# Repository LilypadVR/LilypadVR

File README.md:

# LilypadVR
 Full Body Tracking for VR, based on SlimeVR

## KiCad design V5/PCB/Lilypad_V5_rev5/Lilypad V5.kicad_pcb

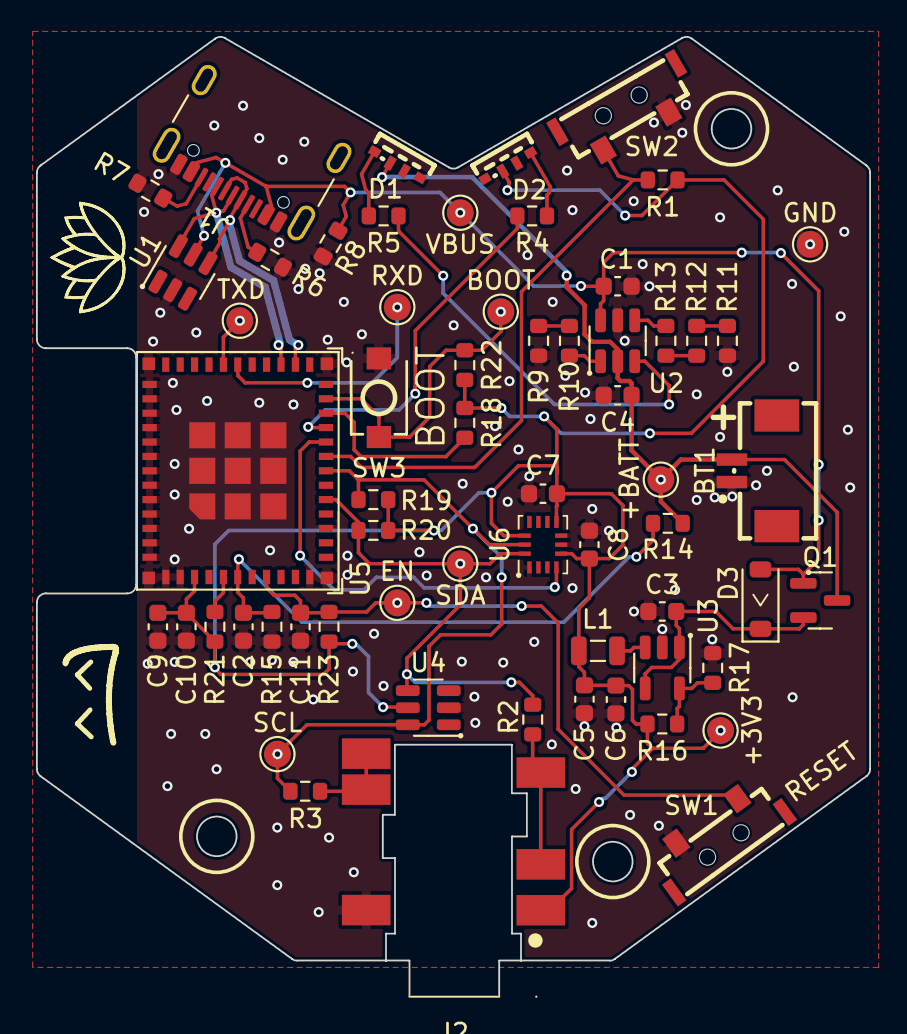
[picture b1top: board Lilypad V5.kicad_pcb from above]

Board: 2 copper layers, 46.3 x 53.3 mm, 61 parts (0 on the bottom side), 33 nets.

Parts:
BT1: Micro-JST; CONN-SMD_2P-P1.25_XUNPU_WAFER-MX1.25-2PWB
C1, C3, C4, C5, C6, C10: 4.7uF; C_0603_1608Metric
C2, C7, C8, C9, C11: 100nF; C_0603_1608Metric
D1: CHARGING_LED; LED-SMD_FM-3510RGBA-SG
D2: STATUS_LED; LED-SMD_FM-3510RGBA-SG
D3: 1N5817W; D_SOD-123
J1: USB-C; USB_C_Receptacle_GCT_USB4105-xx-A_16P_TopMnt_Horizontal
J2: TRRS; AUDIO-SMD_PJ-342C-1
L1: 4.7uH; L_0806_2012Metric
Q1: AO3401A; SOT-23
R1, R6, R7, R9, R10, R18, R19, R20, R21, R22, R23: 5k1; R_0603_1608Metric
R2, R3, R11, R12, R13: 220R; R_0603_1608Metric
R4, R5: 3k; R_0603_1608Metric
R8, R14, R15, R17: 150k; R_0603_1608Metric
R16: 680k; R_0603_1608Metric
SW1: BTN_RESET; SW-SMD_TS-KG012EV
SW2: BTN_USER; SW-SMD_TS-KG012EV
SW3: BTN_BOOT; SW-SMD_L3.9-W3.0-P4.45
TP1: VBUS; TestPoint_Pad_D1.5mm
TP2: +BATT; TestPoint_Pad_D1.5mm
TP3: +3V3; TestPoint_Pad_D1.5mm
TP4: SCL; TestPoint_Pad_D1.5mm
TP5: SDA; TestPoint_Pad_D1.5mm
TP6: TXD; TestPoint_Pad_D1.5mm
TP7: RXD; TestPoint_Pad_D1.5mm
TP8: EN; TestPoint_Pad_D1.5mm
TP9: BOOT; TestPoint_Pad_D1.5mm
TP10: GND; TestPoint_Pad_D1.5mm
U1, U4: SRV05-4; SOT-23-6
U2: BQ21040; SOT-23-6
U3: M3406; SOT-23-5
U5: ESP32-C3-MINI-1-N4; ESP32-C3-MINI-1
U6: BMI270; Bosch_LGA-14_3x2.5mm_P0.5mm

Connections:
+3V3: C5.1, C6.1, C7.2, C8.1, C9.1, C10.1, D2.2 (A), J2.1, L1.2, R1.2, R16.1, R18.2, R19.2, R20.2, R21.2, R22.2, R23.1, TP3.1, U4.5, U5.3 (3V3), U6.5 (VDDIO), U6.8 (VDD), U6.12 (CSB)
+BATT: BT1.1 (+), C4.1, D1.2 (A), Q1.3 (D), R14.1, TP2.1, U2.2 (OUT)
ADC: C2.2, R14.2, R15.1, U5.6 (IO3)
BOOT: R22.1, SW3.1, TP9.1, U5.23 (IO9)
CHRG_LED: R5.2, U2.3 (~CHG)
D+: J1.A6 (D+), J1.B6 (D+), U1.6, U5.27 (IO19)
D-: J1.A7 (D-), J1.B7 (D-), U1.4, U5.26 (IO18)
EN: C11.1, R23.2, SW1.1, TP8.1, U5.8 (EN)
GND: BT1.2 (-), C1.2, C2.1, C3.2, C4.2, C5.2, C6.2, C7.1, C8.2, C9.2, C10.2, C11.2, J1.A1 (GND), J2.2, R6.1, R7.2, R8.2, R9.1, R11.2, R15.2, R17.2, SW1.2, SW2.2, SW3.2, TP10.1, U1.2, U2.5 (GND), U3.2 (GND), U4.2, U5.1 (GND), U5.2 (GND), U5.11 (GND), U5.14 (GND), U5.36 (GND), U5.37 (GND), U5.38 (GND), U5.39 (GND), U5.40 (GND), U5.41 (GND), U5.42 (GND), U5.43 (GND), U5.44 (GND), U5.45 (GND), U5.46 (GND), U5.47 (GND), U5.48 (GND), U5.49 (GND), U5.50 (GND), U5.51 (GND), U5.52 (GND), U5.53 (GND), U6.1 (SDO), U6.6 (GNDIO), U6.7 (GND)
INT_MAIN: U5.20 (IO6), U6.4 (INT1)
IO2: R21.1, U5.5 (IO2)
IO8: R18.1, U5.22 (IO8)
unnamed: D1.1 (RK), R5.1
unnamed: D2.4 (BK), R4.1
unnamed: J1.A5 (CC1), R6.2
unnamed: J1.B5 (CC2), R7.1
unnamed: J2.3, R2.1
unnamed: J2.4, R3.1
unnamed: R9.2, R10.1
unnamed: R11.1, R12.2
unnamed: R12.1, R13.2
unnamed: R13.1, U2.4 (ISET)
unnamed: R10.2, U2.1 (TS)
unnamed: R16.2, R17.1, U3.5 (FB)
unnamed: L1.1, U3.3 (SW)
RXD: TP7.1, U5.30 (RXD0)
SCL: R3.2, R19.1, TP4.1, U4.6, U5.18 (IO4), U6.13 (SCx)
SDA: R2.2, R20.1, TP5.1, U4.4, U5.16 (IO10), U6.14 (SDx)
STATUS_LED: R4.2, U5.21 (IO7)
TXD: TP6.1, U5.31 (TXD0)
USER_IO: R1.1, SW2.1, U5.19 (IO5)
VBUS: C1.1, D3.2 (A), J1.A4 (VBUS), Q1.1 (G), R8.1, TP1.1, U1.5, U2.6 (VIN)
VCC: C3.1, D3.1 (K), Q1.2 (S), U3.1 (RUN), U3.4 (VIN)

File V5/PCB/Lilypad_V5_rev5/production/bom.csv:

Designator,Footprint,Quantity,Value,LCSC Part #
BT1,CONN-SMD_2P-P1.25_XUNPU_WAFER-MX1.25-2PWB,1,Micro-JST,C3029359
"C1, C10, C3, C4, C5, C6",0603,6,4.7uF,C19666
"C11, C2, C7, C8, C9",0603,5,100nF,C14663
D1,LED-SMD_FM-3510RGBA-SG,1,CHARGING_LED,C727903
D2,LED-SMD_FM-3510RGBA-SG,1,STATUS_LED,C727903
D3,D_SOD-123,1,1N5817W,C2828419
J1,USB_C_Receptacle_GCT_USB4105-xx-A_16P_TopMnt_Horizontal,1,USB-C,C2765186
J2,AUDIO-SMD_PJ-342C,1,TRRS,C2837091
L1,0806,1,4.7uH,C98335
Q1,SOT-23,1,AO3401A,C6575062
"R1, R10, R18, R19, R20, R21, R22, R23, R6, R7, R9",0603,11,5k1,C23186
"R11, R12, R13, R2, R3",0603,5,220R,C22962
"R14, R15, R17, R8",0603,4,150k,C22807
R16,0603,1,680k,C25822
"R4, R5",0603,2,3k,C4211
SW1,SW-SMD_TS-KG012EV,1,BTN_RESET,C410363
SW2,SW-SMD_TS-KG012EV,1,BTN_USER,C410363
SW3,SW-SMD_L3.9-W3.0-P4.45,1,BTN_BOOT,C720477
TP1,TestPoint_Pad_D1.5mm,1,VBUS,N/A
TP10,TestPoint_Pad_D1.5mm,1,GND,N/A
TP2,TestPoint_Pad_D1.5mm,1,+BATT,N/A
TP3,TestPoint_Pad_D1.5mm,1,+3V3,N/A
TP4,TestPoint_Pad_D1.5mm,1,SCL,N/A
TP5,TestPoint_Pad_D1.5mm,1,SDA,N/A
TP6,TestPoint_Pad_D1.5mm,1,TXD,N/A
TP7,TestPoint_Pad_D1.5mm,1,RXD,N/A
TP8,TestPoint_Pad_D1.5mm,1,EN,N/A
TP9,TestPoint_Pad_D1.5mm,1,BOOT,N/A
"U1, U4",SOT-23-6,2,SRV05-4,C7420376
U2,SOT-23-6,1,BQ21040,C202311
U3,SOT-23-5,1,M3406,C83224
U5,ESP32-C3-MINI-1,1,ESP32-C3-MINI-1-N4,C2838502
U6,Bosch_LGA-14_3x2.5mm_P0.5mm,1,BMI270,C2836813

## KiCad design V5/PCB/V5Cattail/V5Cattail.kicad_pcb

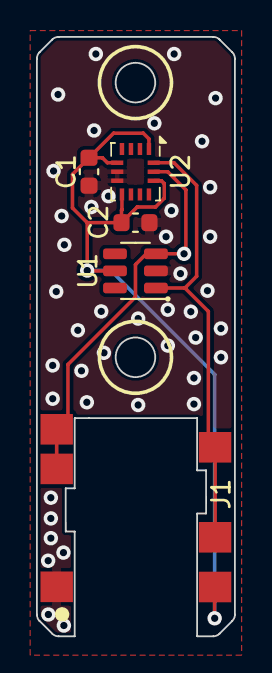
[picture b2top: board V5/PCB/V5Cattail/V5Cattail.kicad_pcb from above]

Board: 2 copper layers, 11.0 x 33.3 mm, 5 parts (0 on the bottom side), 4 nets.

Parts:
C1, C2: 100nF; C_0603_1608Metric
J1: TRRS; AUDIO-SMD_PJ-342C
U1: SRV05-4_C558418; SOT-23-6
U2: BMI270; Bosch_LGA-14_3x2.5mm_P0.5mm

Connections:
+3V3: C1.2, C2.1, J1.1, U1.5, U2.1 (SDO), U2.5 (VDDIO), U2.8 (VDD), U2.12 (CSB)
GND: C1.1, C2.2, J1.2, U1.2, U2.6 (GNDIO), U2.7 (GND)
SCL: J1.4, U1.3, U2.13 (SCx)
SDA: J1.3, U1.1, U2.14 (SDx)

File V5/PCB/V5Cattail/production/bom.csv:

Designator,Footprint,Quantity,Value,LCSC Part #
"C1, C2",0603,2,100nF,C14663
J1,AUDIO-SMD_PJ-342C,1,TRRS,C2837091
U1,SOT-23-6,1,SRV05-4_C558418,C558418
U2,Bosch_LGA-14_3x2.5mm_P0.5mm,1,BMI270,C2836813

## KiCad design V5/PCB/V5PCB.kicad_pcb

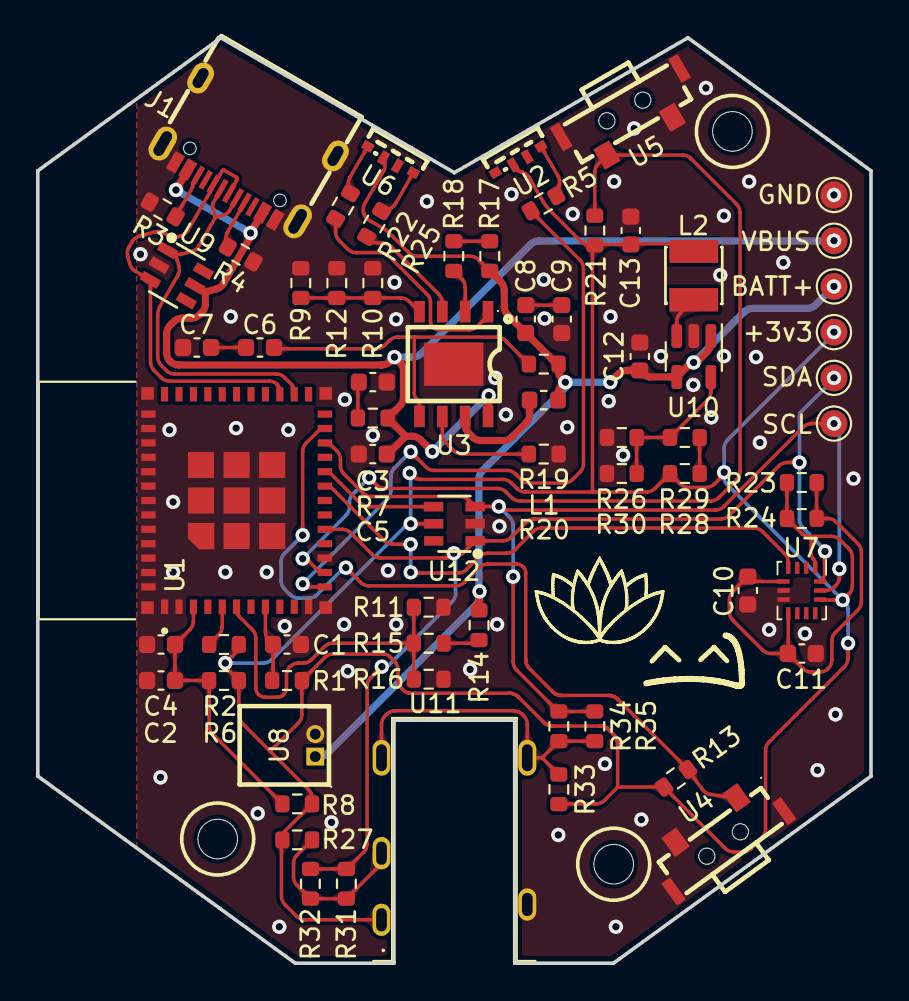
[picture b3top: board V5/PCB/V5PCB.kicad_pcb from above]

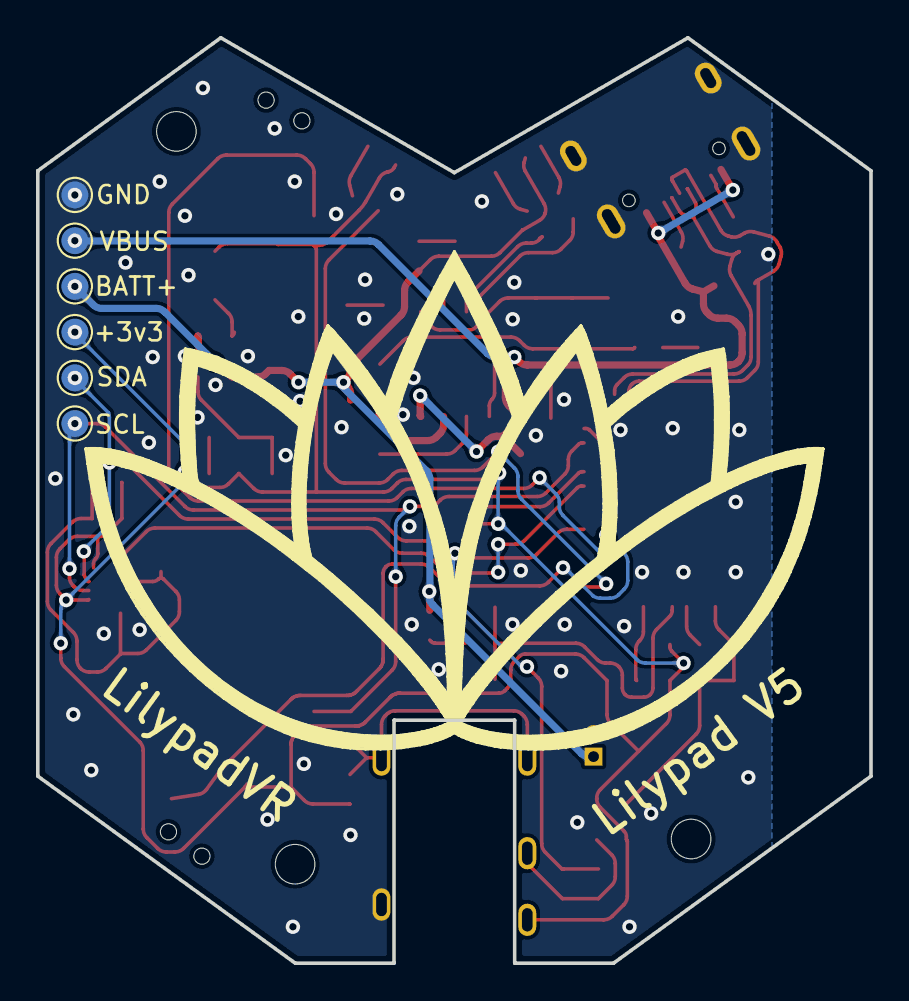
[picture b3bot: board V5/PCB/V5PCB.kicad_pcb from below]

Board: 2 copper layers, 46.3 x 51.4 mm, 75 parts (6 on the bottom side), 40 nets.

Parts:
+3v3, +3v3#2: TestPoint_Pad_D1.5mm
BATT+: TestPoint_Pad_D1.5mm
BATT+#2: TestPoint_Pad_D1.5mm
C1, C4: 1u; C_0603_1608Metric
C2, C10, C11: 100n; C_0603_1608Metric
C3, C5, C6, C7, C8, C9, C13: 10u; C_0603_1608Metric
C12: 4.7u; C_0603_1608Metric
GND: TestPoint_Pad_D1.5mm
GND#2: TestPoint_Pad_D1.5mm
J1: TYPE_C_6PIN_2MD_073; USB-C-SMD_TYPE-C-6PIN-2MD-073
L1: 1uH; L_0603_1608Metric
L2: 2.2uH; IND-SMD_L3.0-W3.0_FNR30XXS
R1, R2, R3, R4, R13, R21, R27, R33: 5k1; R_0603_1608Metric
R5, R22, R25: 3k; R_0603_1608Metric
R6, R8, R17, R18, R23, R24, R31, R32, R34, R35: 470; R_0603_1608Metric
R7: 2r; R_0603_1608Metric
R9, R10, R11, R12, R14, R15, R16, R26, R28, R29, R30: 150k; R_0603_1608Metric
R19: 91k; R_0603_1608Metric
R20: 0r5; R_0603_1608Metric
SCL: TestPoint_Pad_D1.5mm
SCL#2: TestPoint_Pad_D1.5mm
SDA: TestPoint_Pad_D1.5mm
SDA#2: TestPoint_Pad_D1.5mm
U1: ESP32-C3-MINI-1-N4; XCVR_ESP32-C3-MINI-1-N4
U2, U6: FM-3510RGBA-SG; LED-SMD_FM-3510RGBA-SG
U3: IP2312; ESOP-8_L4.9-W3.9-P1.27-LS6.0-BL-EP
U4, U5: TS-KG012EV; SW-SMD_TS-KG012EV
U7: BMI270; Bosch_LGA-14_3x2.5mm_P0.5mm
U8: 1_25T-2AW_C722634; CONN-TH_1.25T-2AW
U9, U12: SRV05-4_C558418; SOT-23-6_L2.9-W1.6-P0.95-LS2.8-BL
U10: M3406; SOT-23-5
U11: ST-0277D00-052-142; AUDIO-TH_ST-0277D00-052-142
VBUS: TestPoint_Pad_D1.5mm
VBUS#2: TestPoint_Pad_D1.5mm

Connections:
+3V3: +3v3.1, +3v3#2.1, C13.1, L2.2, R1.1, R2.2, R6.1, R8.1, R13.2, R21.2, R23.1, R24.1, R27.1, R28.1, R33.1, U2.2 (+), U7.1 (SDO), U7.12 (CSB), U11.1, U12.5
+BATT: BATT+.1, BATT+#2.1, C8.1, C12.1, L1.2, R14.1, R17.1, R20.1, U6.2 (+), U8.1, U10.1 (RUN), U10.4 (VIN)
/ADC: R11.1, R15.2, R16.1, U1.6 (IO3)
/BMI_INT_AUX: U1.20 (IO6), U12.4
/BMI_INT_MAIN: U1.19 (IO5), U7.4 (INT1)
/BOOT: R13.1, U1.23 (IO9), U4.1
/CHARGED_LED: R25.2, U3.3 (D2)
/CHARGING_LED: R22.2, U3.1 (D1)
/EN: C1.1, R1.2, U1.8 (EN)
/GPIO1: R21.1, U1.13 (IO1), U5.1
/GPIO2: R2.1, U1.5 (IO2)
/SCL: R34.1, R35.1, SCL.1, SCL#2.1, U1.22 (IO8), U7.13 (SCx), U12.3
/SDA: R31.1, R32.1, SDA.1, SDA#2.1, U1.16 (IO10), U7.14 (SDx), U12.1
/STATUS_LED: R5.2, U1.12 (IO0)
/USB_D+: J1.A6 (D+), J1.B6 (D+), U1.27 (IO19), U9.3
/USB_D-: J1.A7 (D-), J1.B7 (D-), U1.26 (IO18), U9.1
GND: C1.2, C2.2, C3.2, C4.2, C5.2, C7.2, C9.2, C10.2, C11.2, C12.2, C13.2, GND.1, GND#2.1, J1.A1 (GND), J1.S1 (SHIELD), R3.2, R4.2, R9.1, R10.1, R11.2, R12.1, R16.2, R19.1, R26.2, R30.2, U1.1 (GND), U1.2 (GND), U1.11 (GND), U1.14 (GND), U1.36 (GND), U1.37 (GND), U1.38 (GND), U1.39 (GND), U1.40 (GND), U1.41 (GND), U1.42 (GND), U1.43 (GND), U1.44 (GND), U1.45 (GND), U1.46 (GND), U1.47 (GND), U1.48 (GND), U1.49_1 (GND), U1.49_2 (GND), U1.49_3 (GND), U1.49_4 (GND), U1.49_5 (GND), U1.49_6 (GND), U1.49_7 (GND), U1.49_8 (GND), U1.49_9 (GND), U1.50 (GND), U1.51 (GND), U1.52 (GND), U1.53 (GND), U3.9 (EP), U4.2, U4.3, U4.4, U5.2, U5.3, U5.4, U7.6 (GNDIO), U7.7 (GND), U8.2, U9.2, U10.2 (GND), U11.2, U12.2
unnamed: C3.1, R7.2
unnamed: C6.2, C7.1
unnamed: C8.2, C9.1
unnamed: J1.A5 (CC1), R4.1
unnamed: J1.B5 (CC2), R3.1
unnamed: R5.1, U2.4 (-)
unnamed: R14.2, R15.1
unnamed: R17.2, R18.1
unnamed: R22.1, U6.1 (-)
unnamed: R25.1, U6.4 (-)
unnamed: R27.2, R31.2, R32.2, U11.3
unnamed: R28.2, R29.1
unnamed: R33.2, R34.2, R35.2, U11.4, U11.5
unnamed: C2.1, C4.1, R6.2, R8.2, U1.3 (3V3)
unnamed: C6.1, R20.2, U3.5 (BAT)
unnamed: R19.2, U3.6 (ICHG)
unnamed: R9.2, R10.2, R12.2, U3.4 (NTC)
unnamed: L1.1, U3.7 (SW)
unnamed: R18.2, U3.2 (TEST)
unnamed: C10.1, C11.1, R23.2, R24.2, U7.5 (VDDIO), U7.8 (VDD)
unnamed: R26.1, R29.2, R30.1, U10.5 (FB)
unnamed: L2.1, U10.3 (SW)
VBUS: C5.1, J1.A4 (VBUS), R7.1, U3.8 (VIN), U9.5, VBUS.1, VBUS#2.1

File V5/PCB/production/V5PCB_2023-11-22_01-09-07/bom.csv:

Designator,Footprint,Quantity,Value,LCSC Part #
"C1, C4",0603,2,1u,
"C10, C11, C2",0603,3,100n,
C12,0603,1,4.7u,
"C13, C3, C5, C6, C7, C8, C9",0603,7,10u,
J1,USB-C-SMD_TYPE-C-6PIN-2MD-073,1,TYPE_C_6PIN_2MD_073,
L1,0603,1,1uH,C394948
L2,IND-SMD_L3.0-W3.0_FNR30XXS,1,2.2uH,C167747
"R1, R13, R2, R21, R27, R3, R33, R4",0603,8,5k1,
"R10, R11, R12, R14, R15, R16, R26, R28, R29, R30, R9",0603,11,150k,
"R17, R18, R23, R24, R31, R32, R34, R35, R6, R8",0603,10,470,
R19,0603,1,91k,
R20,0603,1,0r5,
"R22, R25, R5",0603,3,3k,
R7,0603,1,2r,
U1,XCVR_ESP32-C3-MINI-1-N4,1,ESP32-C3-MINI-1-N4,
U10,SOT-23-5,1,M3406,C83224
U11,AUDIO-TH_ST-0277D00-052-142,1,ST-0277D00-052-142,C2837093
"U12, U9",SOT-23-6_L2.9-W1.6-P0.95-LS2.8-BL,2,SRV05-4_C558418,C558418
"U2, U6",LED-SMD_FM-3510RGBA-SG,2,FM-3510RGBA-SG,C727903
U3,ESOP-8_L4.9-W3.9-P1.27-LS6.0-BL-EP,1,~,
"U4, U5",SW-SMD_TS-KG012EV,2,TS-KG012EV,C410363
U7,Bosch_LGA-14_3x2.5mm_P0.5mm,1,BMI270,
U8,CONN-TH_1.25T-2AW,1,1_25T-2AW_C722634,C722634

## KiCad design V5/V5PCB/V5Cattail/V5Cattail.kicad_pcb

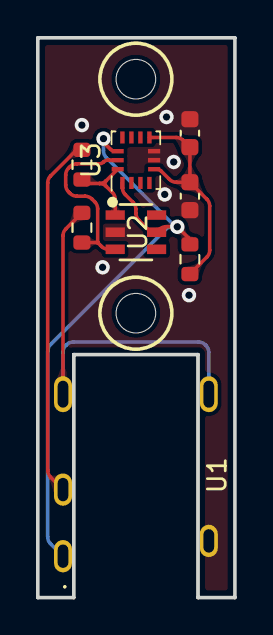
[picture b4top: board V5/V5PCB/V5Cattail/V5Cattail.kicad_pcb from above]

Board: 2 copper layers, 10.9 x 31.1 mm, 8 parts (0 on the bottom side), 7 nets.

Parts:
C1, C2: 100n; C_0603_1608Metric
R1, R2, R3: 1k; R_0603_1608Metric
U1: ST-0277D00-052-142; AUDIO-TH_ST-0277D00-052-142
U2: SRV05-4_C558418; SOT-23-6_L2.9-W1.6-P0.95-LS2.8-BL
U3: BMI270; Bosch_LGA-14_3x2.5mm_P0.5mm

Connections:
+3V3: R3.1, U1.1, U2.5, U3.1 (SDO), U3.12 (CSB)
/SCL: R2.1, U2.3, U3.13 (SCx)
/SDA: R1.1, U2.1, U3.14 (SDx)
GND: C1.2, C2.2, U1.2, U2.2, U3.6 (GNDIO), U3.7 (GND)
unnamed: R1.2, U1.3
unnamed: R2.2, U1.4, U1.5
unnamed: C1.1, C2.1, R3.2, U3.5 (VDDIO), U3.8 (VDD)

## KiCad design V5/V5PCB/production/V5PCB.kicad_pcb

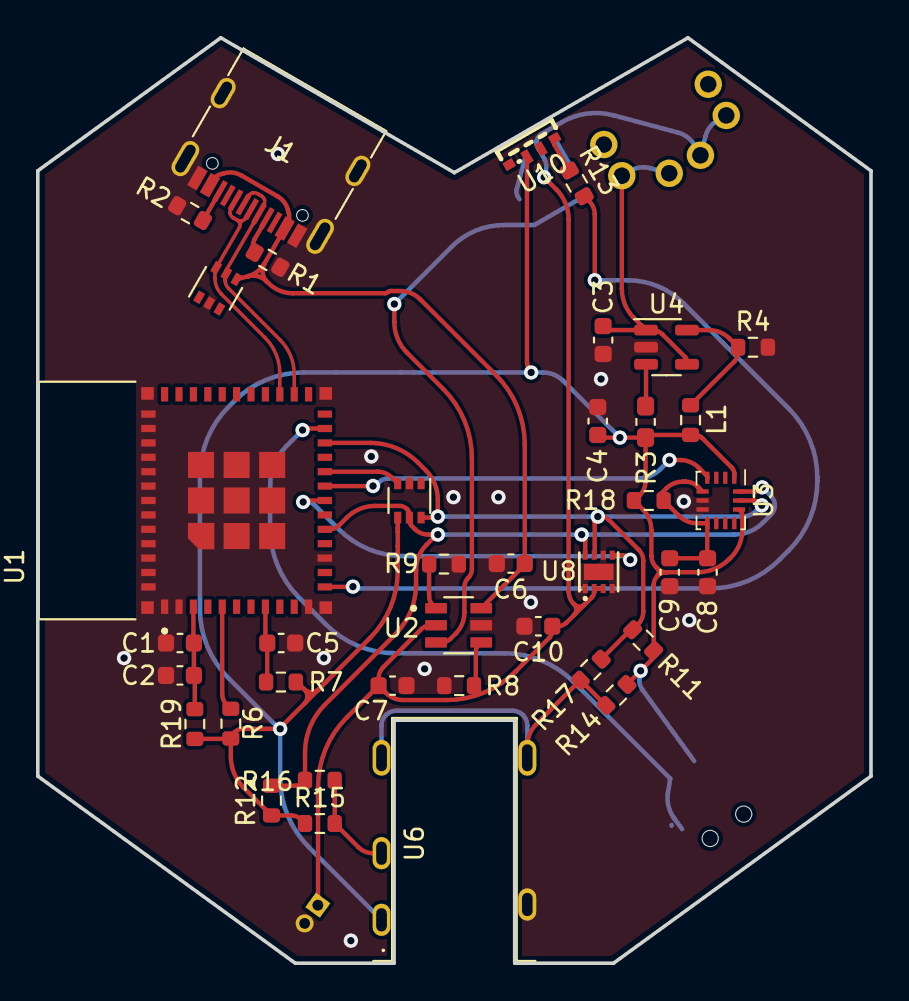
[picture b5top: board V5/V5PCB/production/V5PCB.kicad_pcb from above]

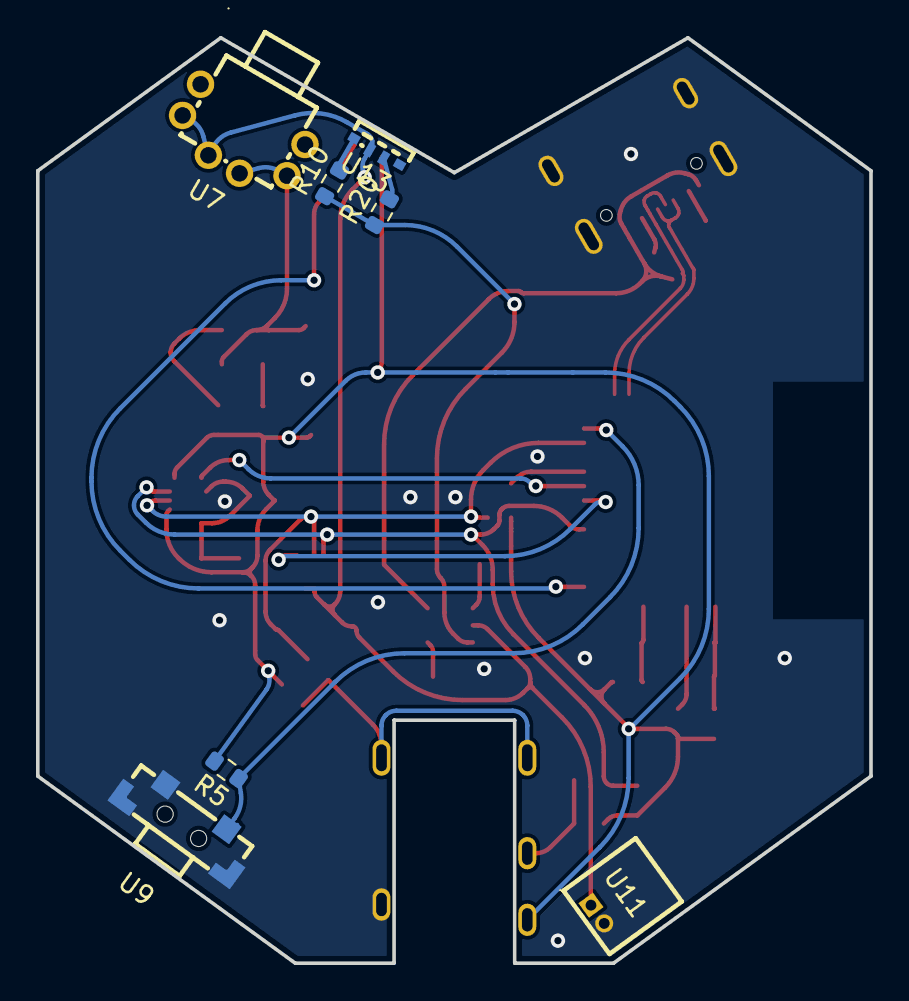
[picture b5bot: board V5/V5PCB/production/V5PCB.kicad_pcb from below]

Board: 2 copper layers, 46.3 x 51.4 mm, 45 parts (7 on the bottom side), 30 nets.

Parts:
C1, C8, C9: 100n; C_0603_1608Metric
C2, C5, C7: 1u; C_0603_1608Metric
C3, C6: 4.7u; C_0603_1608Metric
C4: 10u; C_0603_1608Metric
C10: 0.1u; C_0603_1608Metric
J1: USB_C_Receptacle_USB2.0; USB_C_Receptacle_G-Switch_GT-USB-7010ASV
L1: 2.2uH; L_0603_1608Metric_Pad1.05x0.95mm_HandSolder
R1, R2, R5, R6, R7, R11, R12: 5k1; R_0603_1608Metric
R3: 680k; R_0603_1608Metric
R4: 150k; R_0603_1608Metric
R8: 680R; R_0603_1608Metric
R9: 10k; R_0603_1608Metric
R10, R13, R20: 3k; R_0603_1608Metric
R14, R15: 4k7; R_0603_1608Metric
R16, R17, R18, R19: 220; R_0603_1608Metric
U1: ESP32-C3-MINI-1-N4; XCVR_ESP32-C3-MINI-1-N4
U2: BQ21040DBVR; SOT95P280X145-6N
U3: BMI270; Bosch_LGA-14_3x2.5mm_P0.5mm
U4: M3406; SOT-23-5
U5, U12: SMF05CT1G; SOT-363_SC-70-6
U6: ST-0277D00-052-142; AUDIO-TH_ST-0277D00-052-142
U7: TK-6580A8-1; SW-TH_TK-6580A8-1
U8: MAX17048G+T10; DFN-8_L2.0-W2.0-P0.50-BL-EP
U9: TSB001A3526A02; SW-SMD_YTSB001XXXX
U10, U13: FM-3510RGBA-SG; LED-SMD_FM-3510RGBA-SG
U11: 1_25T-2AW_C722634; CONN-TH_1.25T-2AW

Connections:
+3V3: C4.1, L1.2, R3.1, R5.2, R6.2, R7.1, R11.1, R12.1, R14.1, R15.1, R18.1, R19.1, U3.1 (SDO), U3.12 (CSB), U5.4, U6.1, U10.2 (+)
/BMI_INT_AUX: U1.20 (IO6), U5.3
/BMI_INT_MAIN: U1.19 (IO5), U3.4 (INT1)
/BOOT: R5.1, U1.23 (IO9), U9.1
/EN: C5.1, R7.2, U1.8 (EN)
/GPIO2: R6.1, U1.5 (IO2)
/GPIO4: U1.18 (IO4), U8.5 (ALRT#)
/SCL: R11.2, R17.1, U1.22 (IO8), U3.13 (SCx), U5.6, U8.7 (SCL)
/SDA: R12.2, R16.1, U1.16 (IO10), U3.14 (SDx), U5.5, U8.8 (SDA)
/STATUS_LED: R13.2, U1.12 (IO0)
/USB_D+: J1.A6 (D+), J1.B6 (D+), U1.27 (IO19), U12.6
/USB_D-: J1.A7 (D-), J1.B7 (D-), U1.26 (IO18), U12.5
/VCC_RAW: C7.1, C10.1, U2.2 (OUT), U7.2, U7.5, U8.2 (CELL), U8.3 (VDD), U11.1, U13.2 (+)
GND: C1.2, C2.2, C3.2, C4.2, C5.2, C6.2, C7.2, C8.2, C9.2, C10.2, J1.A1 (GND), J1.A12 (GND), J1.B1 (GND), J1.B12 (GND), J1.S1 (SHIELD), R1.2, R2.2, R4.2, R8.1, R9.1, U1.1 (GND), U1.2 (GND), U1.11 (GND), U1.14 (GND), U1.36 (GND), U1.37 (GND), U1.38 (GND), U1.39 (GND), U1.40 (GND), U1.41 (GND), U1.42 (GND), U1.43 (GND), U1.44 (GND), U1.45 (GND), U1.46 (GND), U1.47 (GND), U1.48 (GND), U1.49_1 (GND), U1.49_2 (GND), U1.49_3 (GND), U1.49_4 (GND), U1.49_5 (GND), U1.49_6 (GND), U1.49_7 (GND), U1.49_8 (GND), U1.49_9 (GND), U1.50 (GND), U1.51 (GND), U1.52 (GND), U1.53 (GND), U2.5 (GND), U3.6 (GNDIO), U3.7 (GND), U4.2 (GND), U5.2, U6.2, U8.1 (CTG), U8.4 (GND), U8.6 (QSTRT), U8.9 (EP), U9.2, U9.3, U9.4, U11.2, U12.2
unnamed: J1.A5 (CC1), R1.1
unnamed: J1.B5 (CC2), R2.1
unnamed: R10.2, U13.1 (-)
unnamed: R13.1, U10.4 (-)
unnamed: R14.2, R17.2, U6.4, U6.5
unnamed: R15.2, R16.2, U6.3
unnamed: R20.2, U13.3 (-)
unnamed: C1.1, C2.1, R19.2, U1.3 (3V3)
unnamed: R8.2, U2.4 (ISET)
unnamed: R9.2, U2.1 (TS)
unnamed: R10.1, R20.1, U2.3 (~CHG)
unnamed: C8.1, C9.1, R18.2, U3.5 (VDDIO), U3.8 (VDD)
unnamed: R3.2, R4.1, U4.5 (FB)
unnamed: L1.1, U4.3 (SW)
VBUS: C6.1, J1.A4 (VBUS), J1.A9 (VBUS), J1.B4 (VBUS), J1.B9 (VBUS), U2.6 (VIN), U12.4
VCC: C3.1, U4.1 (RUN), U4.4 (VIN), U7.4, U7.6

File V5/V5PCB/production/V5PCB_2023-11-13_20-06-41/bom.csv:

Designator,Footprint,Quantity,Value,LCSC Part #
"C1, C8, C9",0603,3,100n,
C10,0603,1,0.1u,
"C2, C5, C7",0603,3,1u,
"C3, C6",0603,2,4.7u,
C4,0603,1,10u,
J1,USB_C_Receptacle_G-Switch_GT-USB-7010ASV,1,USB_C_Receptacle_USB2.0,
L1,0603,1,2.2uH,
"R1, R11, R12, R2, R5, R6, R7",0603,7,5k1,
"R10, R13, R20",0603,3,3k,
"R14, R15",0603,2,4k7,
"R16, R17, R18, R19",0603,4,220,
R3,0603,1,680k,
R4,0603,1,150k,
R8,0603,1,680R,
R9,0603,1,10k,
U1,XCVR_ESP32-C3-MINI-1-N4,1,ESP32-C3-MINI-1-N4,
"U10, U13",LED-SMD_FM-3510RGBA-SG,2,FM-3510RGBA-SG,C727903
U11,CONN-TH_1.25T-2AW,1,1_25T-2AW_C722634,C722634
"U12, U5",SOT-363_SC-70-6,2,SMF05CT1G,
U2,SOT95P280X145-6N,1,BQ21040DBVR,
U3,Bosch_LGA-14_3x2.5mm_P0.5mm,1,BMI270,
U4,SOT-23-5,1,M3406,C83224
U6,AUDIO-TH_ST-0277D00-052-142,1,ST-0277D00-052-142,C2837093
U7,SW-TH_TK-6580A8-1,1,TK-6580A8-1,C528772
U8,DFN-8_L2.0-W2.0-P0.50-BL-EP,1,MAX17048G+T10,C2682616
U9,SW-SMD_YTSB001XXXX,1,TSB001A3526A02,C2888889

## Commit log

2023-11-26 File path restructuring
2023-11-26 V4 Photoshoot Push 1
2023-11-26 V4 Photoshoot push 2
2023-11-26 V4 Photoshoot push 3
2023-11-26 V4 Photoshoot push 4
2023-11-26 V4 Photoshoot push 5
2023-11-26 V4 Photoshoot push 6
2023-12-01 test
2023-12-16 reorganizing CAD files
2024-04-02 Backup
2024-05-07 V5 CAD started
2024-05-24 Overdue backup
2024-06-06 Prototype Model/PCB Updates
2024-07-05 Model Updates, PCB Fixes
